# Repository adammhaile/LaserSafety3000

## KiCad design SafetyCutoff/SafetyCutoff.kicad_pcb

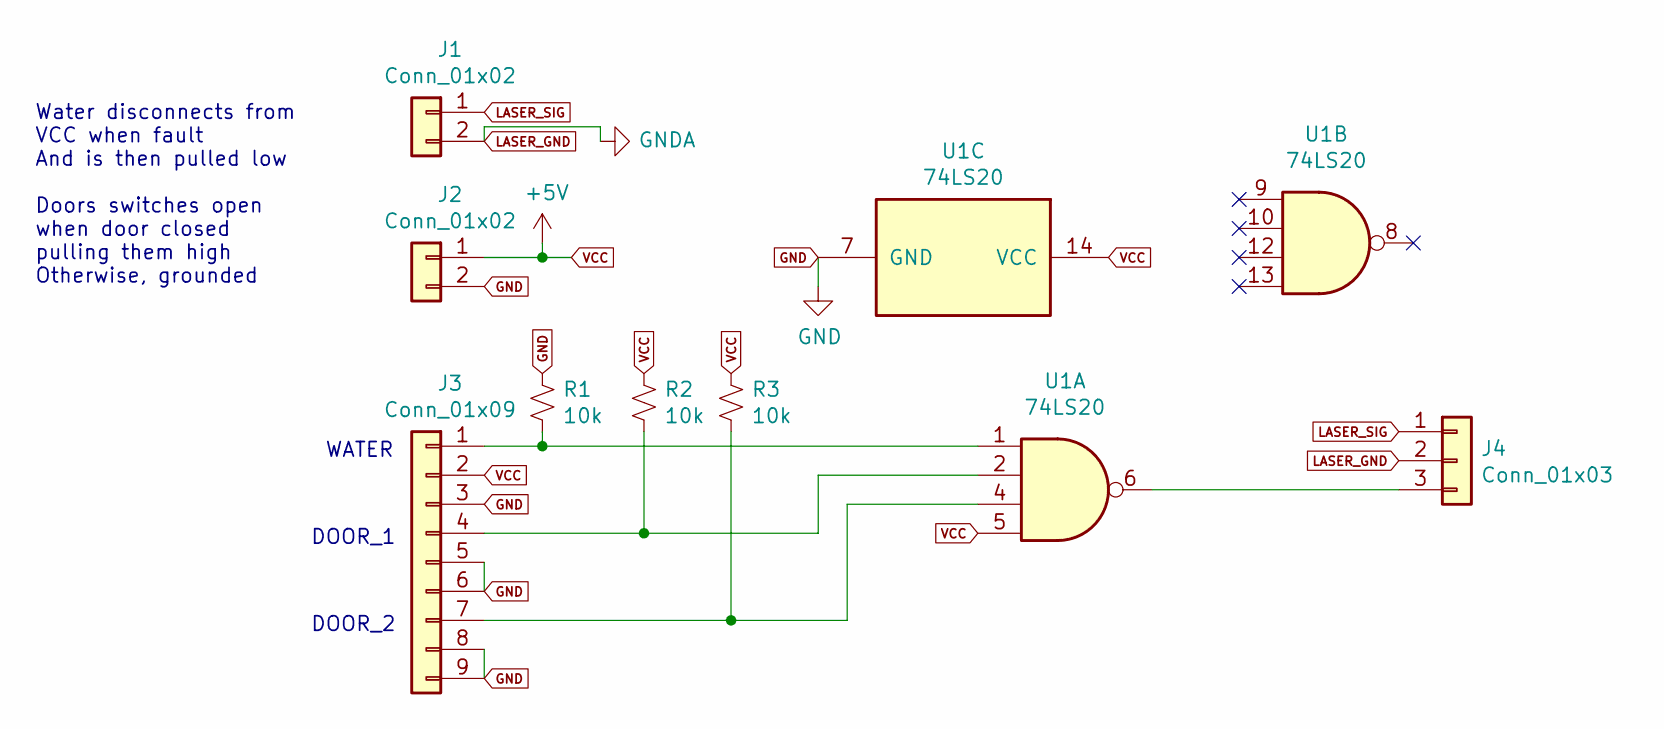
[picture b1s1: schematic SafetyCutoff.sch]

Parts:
J1, J2: Conn_01x02; PinSocket_1x02_P2.54mm_Vertical
J3: Conn_01x09; PinSocket_1x09_P2.54mm_Vertical
J4: Conn_01x03; PinSocket_1x03_P2.54mm_Vertical
R1, R2, R3: 10k; R_Axial_DIN0207_L6.3mm_D2.5mm_P10.16mm_Horizontal
U1: 74LS20; DIP-14_W7.62mm

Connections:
GND: J2.2, J3.3, J3.5, J3.6, J3.8, J3.9, R1.1, U1.7 (GND)
LASER_GND: J1.2, J4.2
LASER_SIG: J1.1, J4.1
unnamed: J3.1, R1.2, U1.1
unnamed: J3.4, R2.2, U1.2
unnamed: J3.7, R3.2, U1.4
unnamed: J4.3, U1.6
VCC: J2.1, J3.2, R2.1, R3.1, U1.5, U1.14 (VCC)

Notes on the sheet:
WATER
DOOR_1
DOOR_2
Water disconnects from VCC when fault And is then pulled low Doors switches open when door closed pulling them high Otherwise, grounded

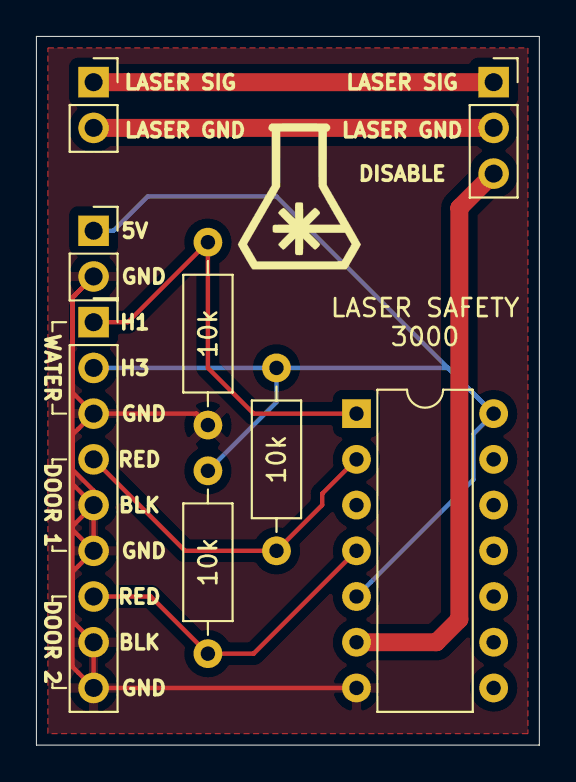
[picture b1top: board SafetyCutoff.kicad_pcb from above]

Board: 2 copper layers, 27.9 x 39.4 mm, 8 parts (0 on the bottom side), 8 nets.
